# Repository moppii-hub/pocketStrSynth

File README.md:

# What's pocketStrSynth?
This is a small-size synthesizer using an Arduino.
The original idea is from [dspsynth.eu by Jan Ostman](https://web.archive.org/web/20180817050935/http://blog.dspsynth.eu/how-to-build-a-string-synth/).
Now this website had already closed, but there is [the related article in Hackaday.com wrote by Elliot Williams](https://hackaday.com/2016/02/23/a-slew-of-open-source-synthesizers/), we can also refer this.  
  
Arduinoを使った小型のシンセサイザーです。  
音源部は[dspsynth.eu](https://web.archive.org/web/20180817050935/http://blog.dspsynth.eu/how-to-build-a-string-synth/)というサイトのソースコードを流用しています。  
現在このWebサイトは閉鎖していますが、[Hackaday.com](https://hackaday.com/2016/02/23/a-slew-of-open-source-synthesizers/)に同じコードを用いて別の方が執筆した記事がありますので、よろしければそちらもご参考ください。  

# リポジトリの内容
このリポジトリには以下の内容が含まれます。
 - Arduinoプログラムのソースコード
 - 外装設計データ
 - 基板設計データ（回路図、KiCadプロジェクト一式、及び基板発注に使うGerberデータ）
 - その他（写真・演奏例）

# 機能説明
このシンセサイザーは以下の機能を備えています。
 - 8個の鍵盤…演奏に使用します。6キー以上を同時押しし続けると設定モード/演奏モードを切り替えます。
 - 5つのDIPスイッチ…音階が変わります。（キーマトリクスの回路接続の変更スイッチです）
 - 3つのツマミ…それぞれ以下の機能があります。
   - 左　：アタック/リリースタイムの調節（設定モード時は、8つのキーの音階範囲が変わります）
   - 中央：デチューン量の調節（設定モード時は、スケールを変更します。メジャーとペンタの2種）
   - 右　：オクターブシフト４段階（設定モード時は、調声が変わります。Cから+15段階。）
 - ボタン電池（CR2032 3V）2個で動作します。

# 注意点
 - 基板上のコネクタ（ピンヘッダ）は、拡張または実験用です。演奏には直接必要はありません。
 - 電源スイッチON状態でUSBケーブルを接続すると、電池側またはUSB側に逆電圧が掛かります。

# その他写真

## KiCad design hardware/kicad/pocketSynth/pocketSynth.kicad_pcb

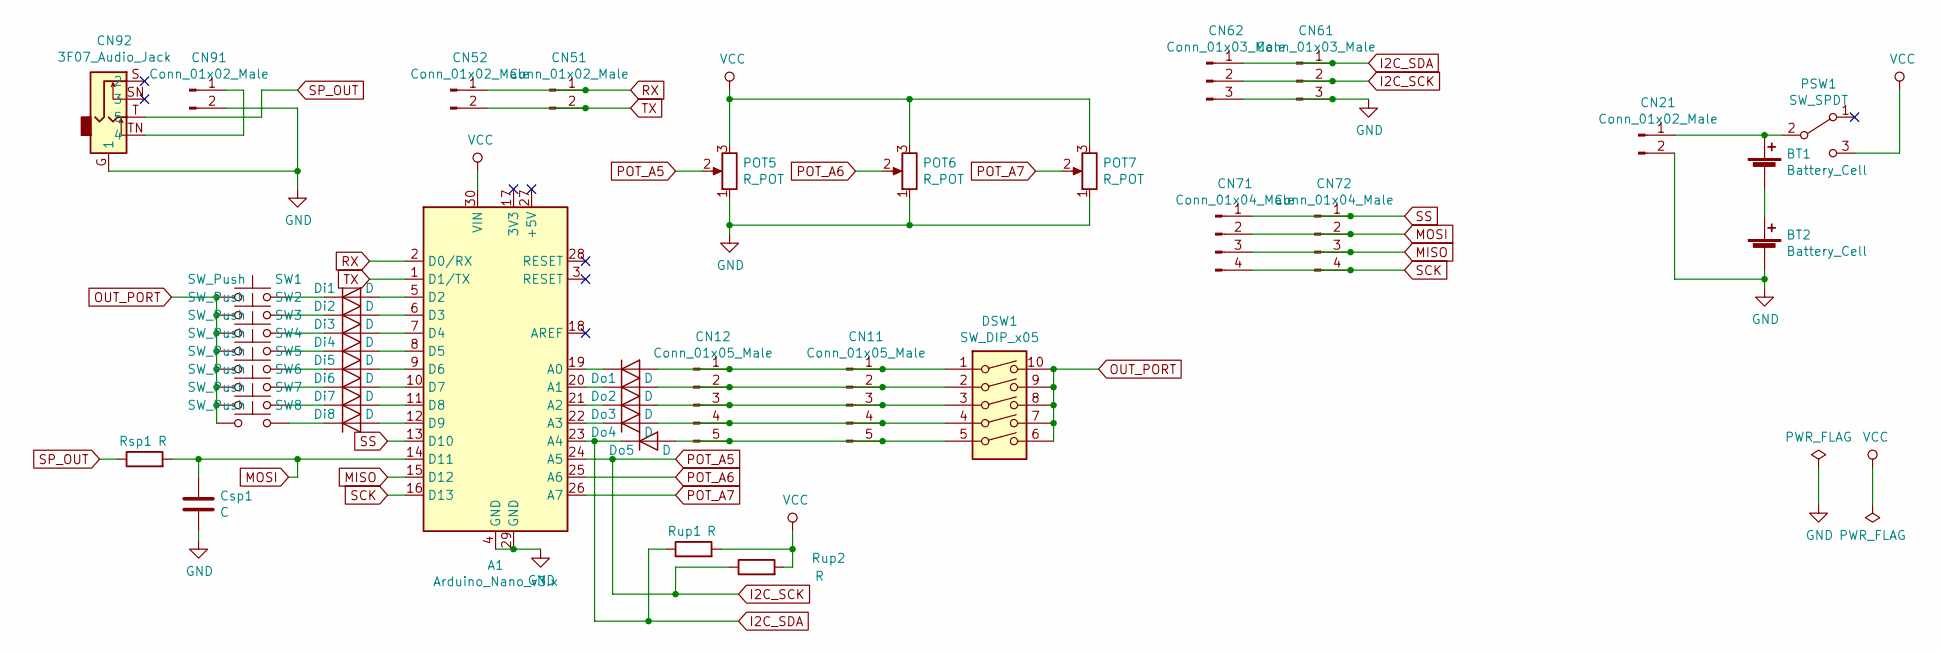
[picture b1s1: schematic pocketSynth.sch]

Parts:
A1: Arduino_Nano_v3.x; Arduino_Nano
BT1, BT2: Battery_Cell; BatteryHolder_Keystone_107_1x23mm
CN11, CN12: Conn_01x05_Male; PinHeader_1x05_P2.54mm_Vertical
CN21, CN51, CN52, CN91: Conn_01x02_Male; PinHeader_1x02_P2.54mm_Vertical
CN61, CN62: Conn_01x03_Male; PinHeader_1x03_P2.54mm_Vertical
CN71, CN72: Conn_01x04_Male; PinHeader_1x04_P2.54mm_Vertical
CN92: 3F07_Audio_Jack
Csp1: C; C_Disc_D3.0mm_W1.6mm_P2.50mm
DSW1: SW_DIP_x05; SW_DIP_SPSTx05_Slide_9.78x14.88mm_W7.62mm_P2.54mm
Di1, Di2, Di3, Di4, Di5, Di6, Di7, Di8: D; D_SOD-323
Do1, Do2, Do3, Do4, Do5: D; D_SOD-323
POT5, POT6, POT7: R_POT; Potentiometer_Alpha_RD901F-40-00D_Single_Vertical
PSW1: SW_SPDT; SW_CuK_OS102011MA1QN1_SPDT_Angled
Rsp1: R; R_0603_1608Metric_Pad1.05x0.95mm_HandSolder
Rup1, Rup2: R; R_0603_1608Metric_Pad1.05x0.95mm_HandSolder
SW1, SW2, SW3, SW4, SW5, SW6, SW7, SW8: SW_Push; SW_PUSH_6mm_H5mm

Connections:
GND: A1.4 (GND), A1.29 (GND), BT2.2 (-), CN21.2, CN61.3, CN62.3, CN91.2, CN92.G (1), Csp1.2, POT5.1, POT6.1, POT7.1
I2C_SCK: A1.24 (A5), CN61.2, CN62.2, POT5.2, Rup2.1
I2C_SDA: A1.23 (A4), CN61.1, CN62.1, Do5.1 (K), Rup1.1
MISO: A1.15 (D12), CN71.3, CN72.3
MOSI: A1.14 (D11), CN71.2, CN72.2, Csp1.1, Rsp1.2
unnamed: A1.5 (D2), Di1.2 (A)
unnamed: A1.6 (D3), Di2.2 (A)
unnamed: A1.7 (D4), Di3.2 (A)
unnamed: A1.8 (D5), Di4.2 (A)
unnamed: A1.9 (D6), Di5.2 (A)
unnamed: A1.10 (D7), Di6.2 (A)
unnamed: A1.11 (D8), Di7.2 (A)
unnamed: A1.12 (D9), Di8.2 (A)
unnamed: A1.19 (A0), Do1.1 (K)
unnamed: A1.20 (A1), Do2.1 (K)
unnamed: A1.21 (A2), Do3.1 (K)
unnamed: A1.22 (A3), Do4.1 (K)
unnamed: BT1.1 (+), CN21.1, PSW1.2 (B)
unnamed: BT1.2 (-), BT2.1 (+)
unnamed: CN11.1, CN12.1, DSW1.1, Do1.2 (A)
unnamed: CN11.2, CN12.2, DSW1.2, Do2.2 (A)
unnamed: CN11.3, CN12.3, DSW1.3, Do3.2 (A)
unnamed: CN11.4, CN12.4, DSW1.4, Do4.2 (A)
unnamed: CN11.5, CN12.5, DSW1.5, Do5.2 (A)
unnamed: CN91.1, CN92.TN (4)
unnamed: Di1.1 (K), SW1.2
unnamed: Di2.1 (K), SW2.2
unnamed: Di3.1 (K), SW3.2
unnamed: Di4.1 (K), SW4.2
unnamed: Di5.1 (K), SW5.2
unnamed: Di6.1 (K), SW6.2
unnamed: Di7.1 (K), SW7.2
unnamed: Di8.1 (K), SW8.2
OUT_PORT: DSW1.6, DSW1.7, DSW1.8, DSW1.9, DSW1.10, SW1.1, SW2.1, SW3.1, SW4.1, SW5.1, SW6.1, SW7.1, SW8.1
POT_A6: A1.25 (A6), POT6.2
POT_A7: A1.26 (A7), POT7.2
RX: A1.2 (D0/RX), CN51.1, CN52.1
SCK: A1.16 (D13), CN71.4, CN72.4
SP_OUT: CN92.T (5), Rsp1.1
SS: A1.13 (D10), CN71.1, CN72.1
TX: A1.1 (D1/TX), CN51.2, CN52.2
VCC: A1.30 (VIN), POT5.3, POT6.3, POT7.3, PSW1.3 (C), Rup1.2, Rup2.2

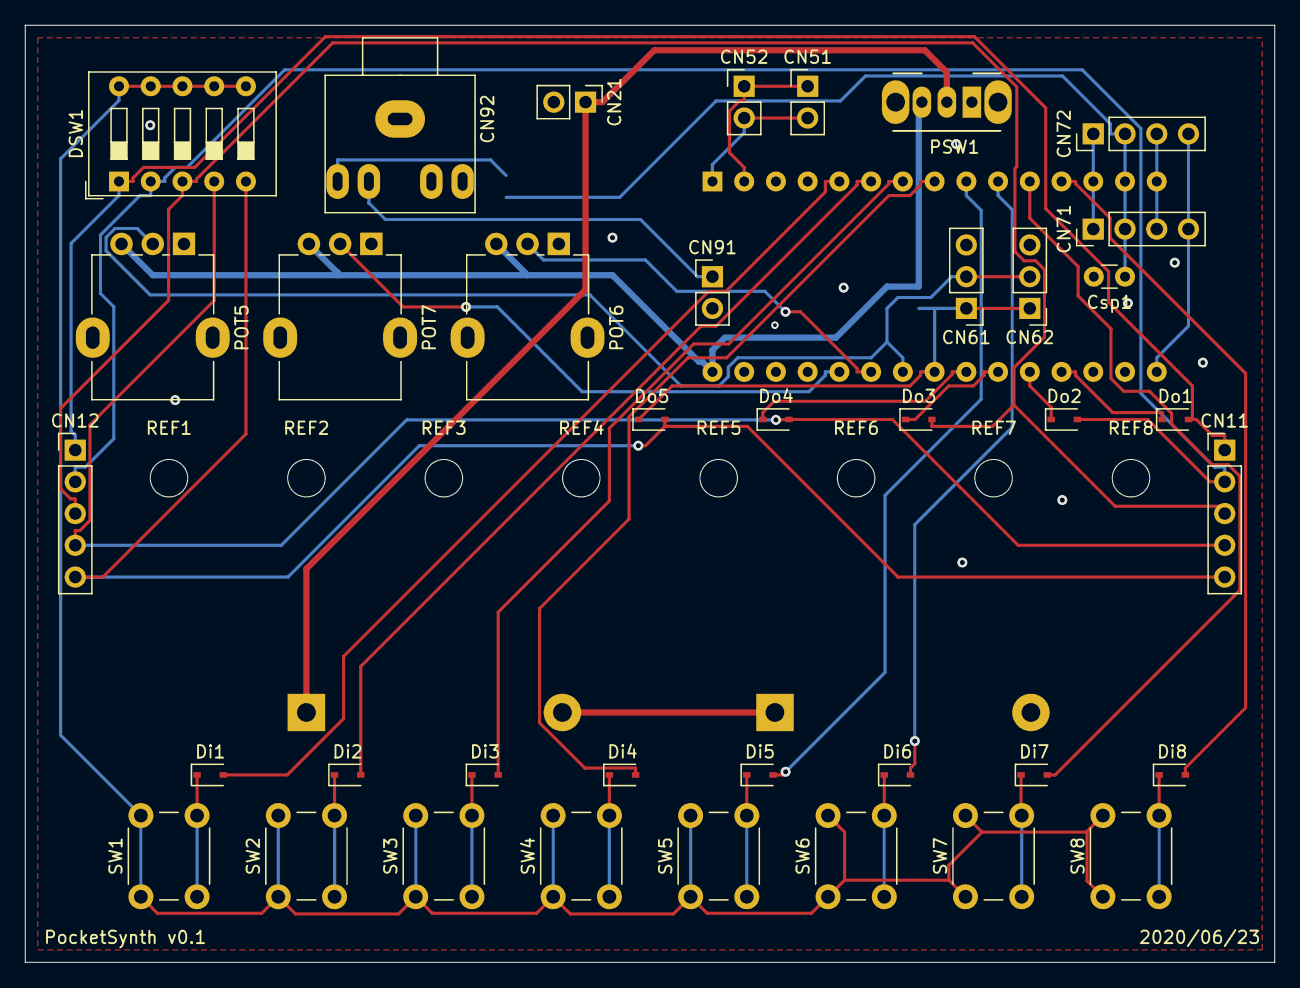
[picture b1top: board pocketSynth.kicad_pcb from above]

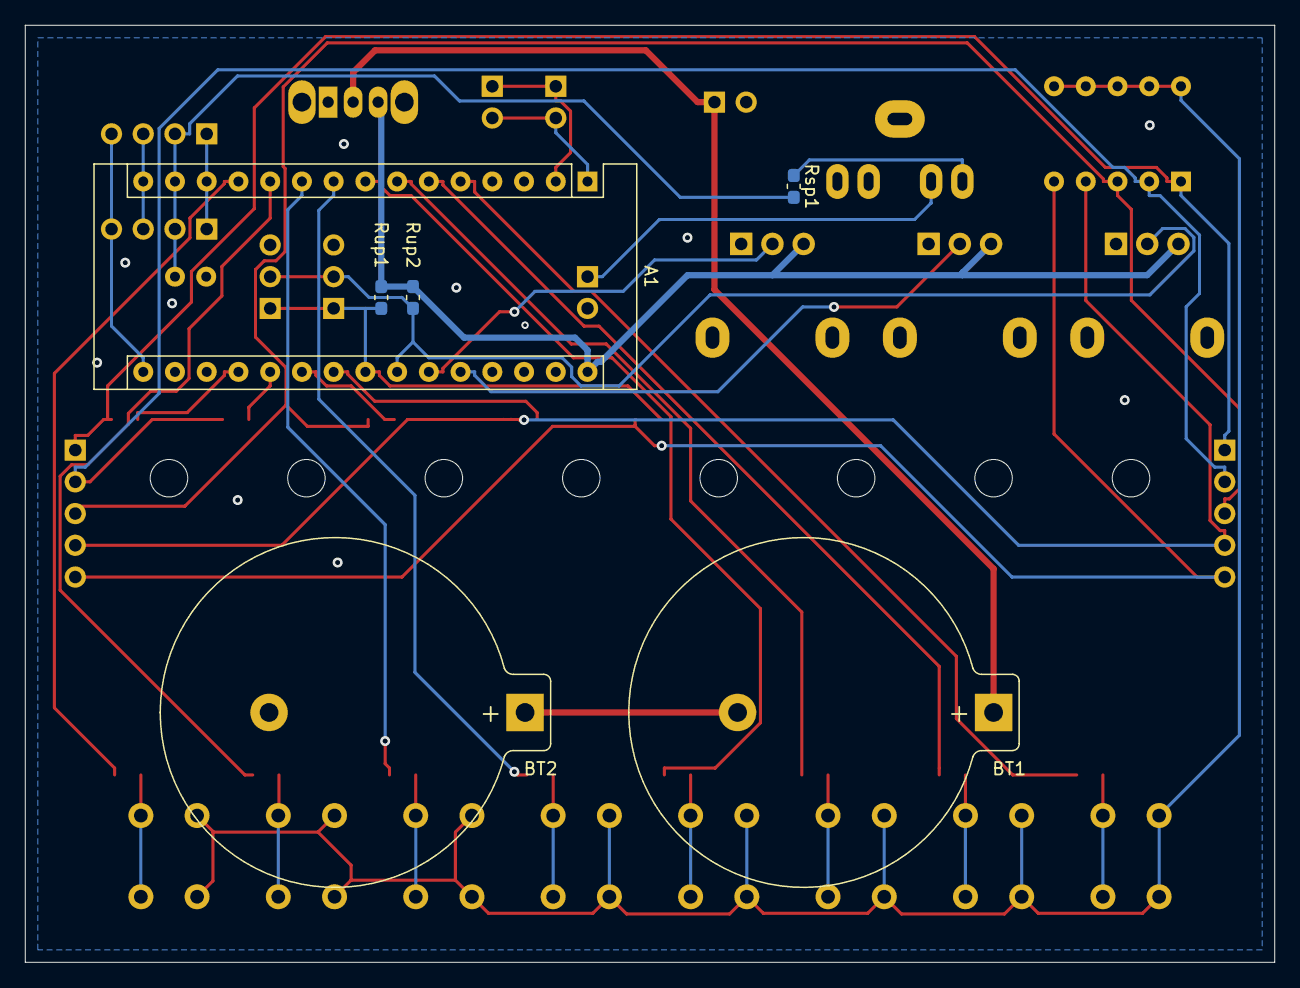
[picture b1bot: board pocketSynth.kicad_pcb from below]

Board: 2 copper layers, 100.0 x 75.0 mm, 52 parts (6 on the bottom side), 42 nets.

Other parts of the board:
REF1, REF2, REF3, REF4, REF5, REF6, REF7, REF8: MountingHole_3mm

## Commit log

2020-07-05 1st commit
2020-07-05 changed readme
2020-07-05 add schematics
